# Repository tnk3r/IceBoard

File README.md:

# IceBoard
Python Controlled Arduino PWM Breakout for Controlling PC Fans.

This is the 'firmware' for the IceBoard Fan Controller. use Arduino Software to upload/compile onto your Arduino Nano.

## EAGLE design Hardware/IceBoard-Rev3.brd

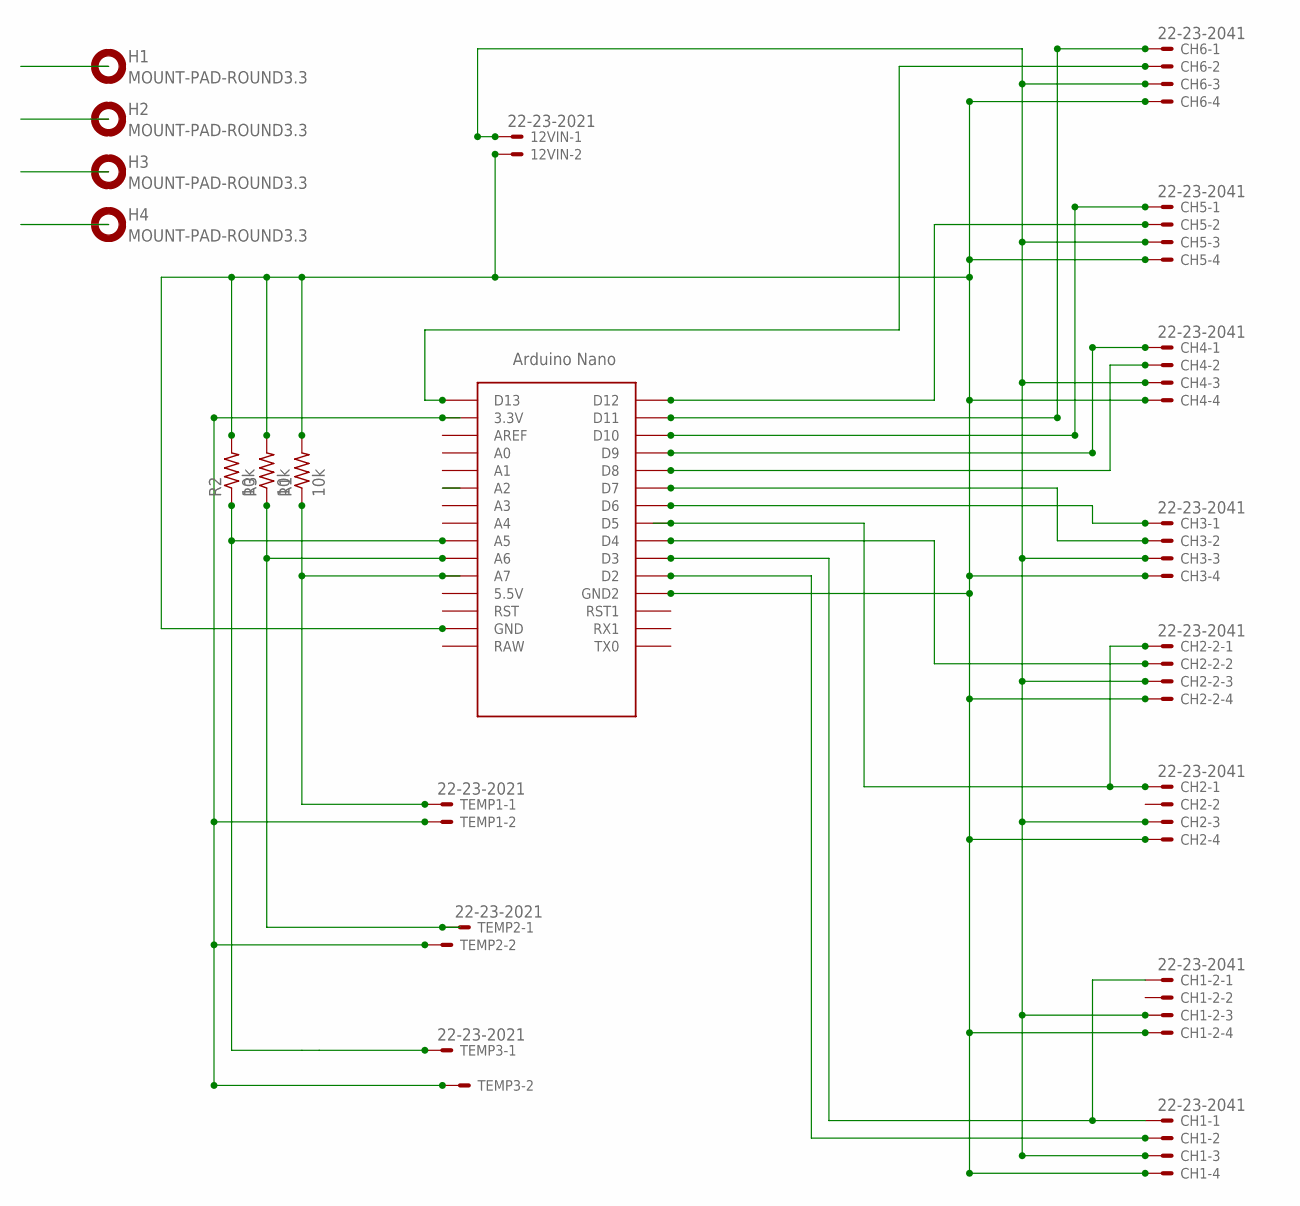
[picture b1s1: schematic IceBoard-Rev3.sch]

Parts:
12VIN: 22-23-2021
CH1, CH1-2, CH2, CH2-2, CH3, CH4, CH5, CH6: 22-23-2041
H1, H2, H3, H4: MOUNT-PAD-ROUND3.3; 3,3-PAD
R1, R2, R3: 10k; R0805
TEMP1, TEMP2, TEMP3: 22-23-2021
U$1: NANO

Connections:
10K: TEMP1.2, TEMP2.2, TEMP3.2, U$1.3.3V
GND: 12VIN.2, CH1.4, CH1-2.4, CH2.4, CH2-2.4, CH3.4, CH4.4, CH5.4, CH6.4, R1.2, R2.2, R3.2, U$1.GND, U$1.GND1 (GND2)
unnamed: CH5.1, U$1.D10
unnamed: CH6.1, U$1.D11
unnamed: CH1.1, CH1-2.1, U$1.D3
unnamed: CH2.1, CH2-2.1, U$1.D5
unnamed: CH3.1, U$1.D6
unnamed: CH4.1, U$1.D9
unnamed: R3.1, TEMP2.1, U$1.A6
unnamed: 12VIN.1, CH1.3, CH1-2.3, CH2.3, CH2-2.3, CH3.3, CH4.3, CH5.3, CH6.3
unnamed: CH6.2, U$1.D13
unnamed: CH5.2, U$1.D12
unnamed: R1.1, TEMP1.1, U$1.A7
unnamed: CH4.2, U$1.D8
unnamed: CH3.2, U$1.D7
unnamed: CH2-2.2, U$1.D4
unnamed: CH1.2, U$1.D2
unnamed: R2.1, TEMP3.1, U$1.A5

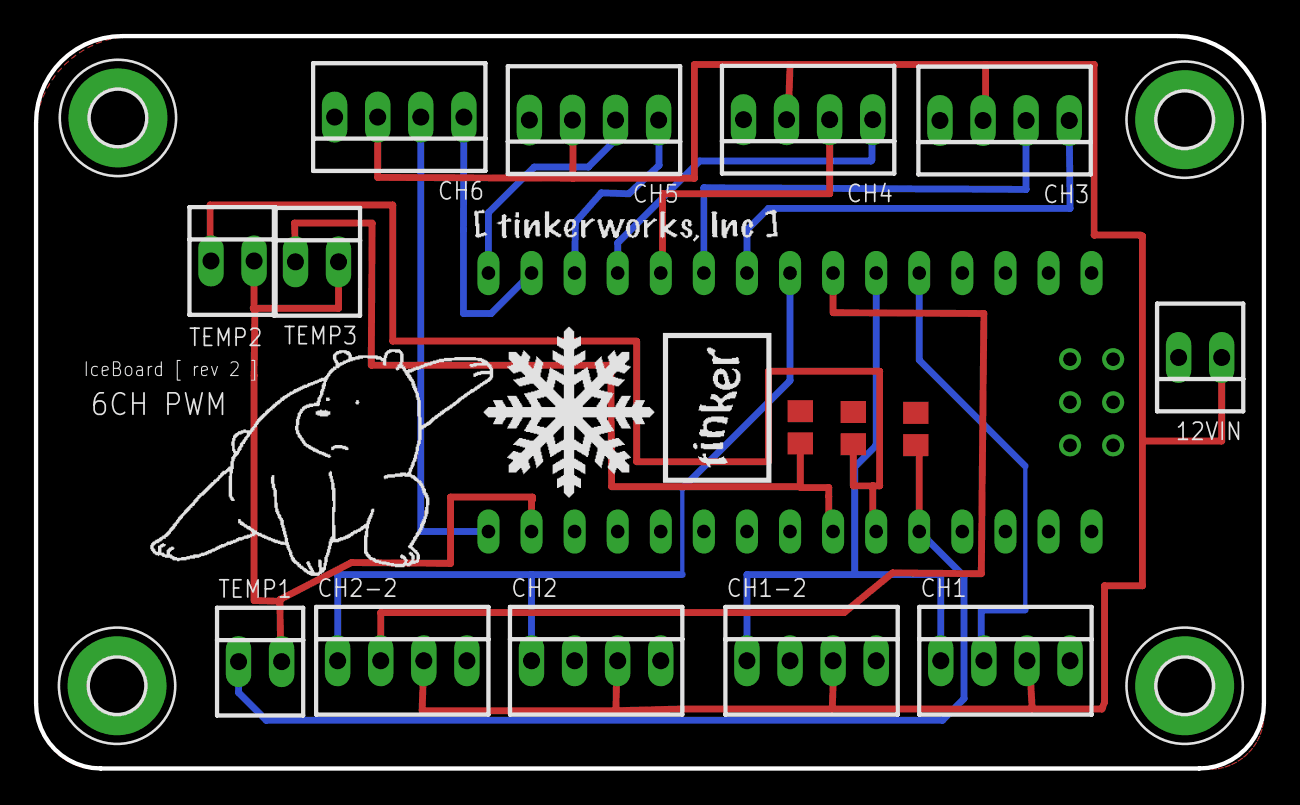
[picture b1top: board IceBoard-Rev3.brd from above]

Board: 2 copper layers, 72.4 x 43.2 mm, 20 parts (0 on the bottom side), 18 nets.

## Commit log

2017-04-24 IceBoard Rev2 Hardware
2017-04-27 IceBoard Rev3 Hardware
2017-05-19 Version Control 1.5 IceBoard Firmware
2017-05-19 IceBoard Rev3 Hardware firmware
2017-05-19 IceBoard v155 update, only writes EEprom if New setting is found
2017-05-19 IceBoard v155 update, only writes EEprom if New setting is found.
2017-06-07 rev3 board
2017-07-22 Ver160 Firmware, added Temperature on 3 channels. Python for MAth
2017-07-24 V175 commit, July 24 2017
